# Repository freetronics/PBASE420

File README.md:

Freetronics ProtoBase 420
=========================
Copyright 2015 Freetronics Pty Ltd  
Freetronics site:  www.freetronics.com  
Freetronics email: info@freetronics.com  

ProtoBase 420 is a prototyping circuit board designed to follow the
same format as common 400-point solderless breadboards. It can be
used by soldering parts in place, or a solderless breadboard can be
adhered to the top.

Includes a linear voltage regulator with switchable 3.3V / 5V output,
and a 2.1mm DC jack for power input.

Features:

 * Prototyping area
 * Switchable 3.3V / 5V voltage regulator
 * Power LED
 * 2.1mm DC power socket
 * Overlay guide where you need it (both top and bottom)
 * 3.2mm mounting holes for M3 bolts

You can view more at our product page at:

  http://www.freetronics.com/pbase420

INSTALLATION
------------
The design is saved as an EAGLE project. EAGLE PCB design software is
available from www.cadsoftusa.com free for non-commercial use. To use
this project download it and place the directory containing these files
into the "eagle" directory on your computer. Then open EAGLE and
navigate to Projects -> eagle -> PBASE420.

DISTRIBUTION
------------
The specific terms of distribution of this project are governed by the
license referenced below.

LICENSE
-------
Licensed under the TAPR Open Hardware License (www.tapr.org/OHL).
The "license" folder within this repository also contains a copy of
this license in plain text format.

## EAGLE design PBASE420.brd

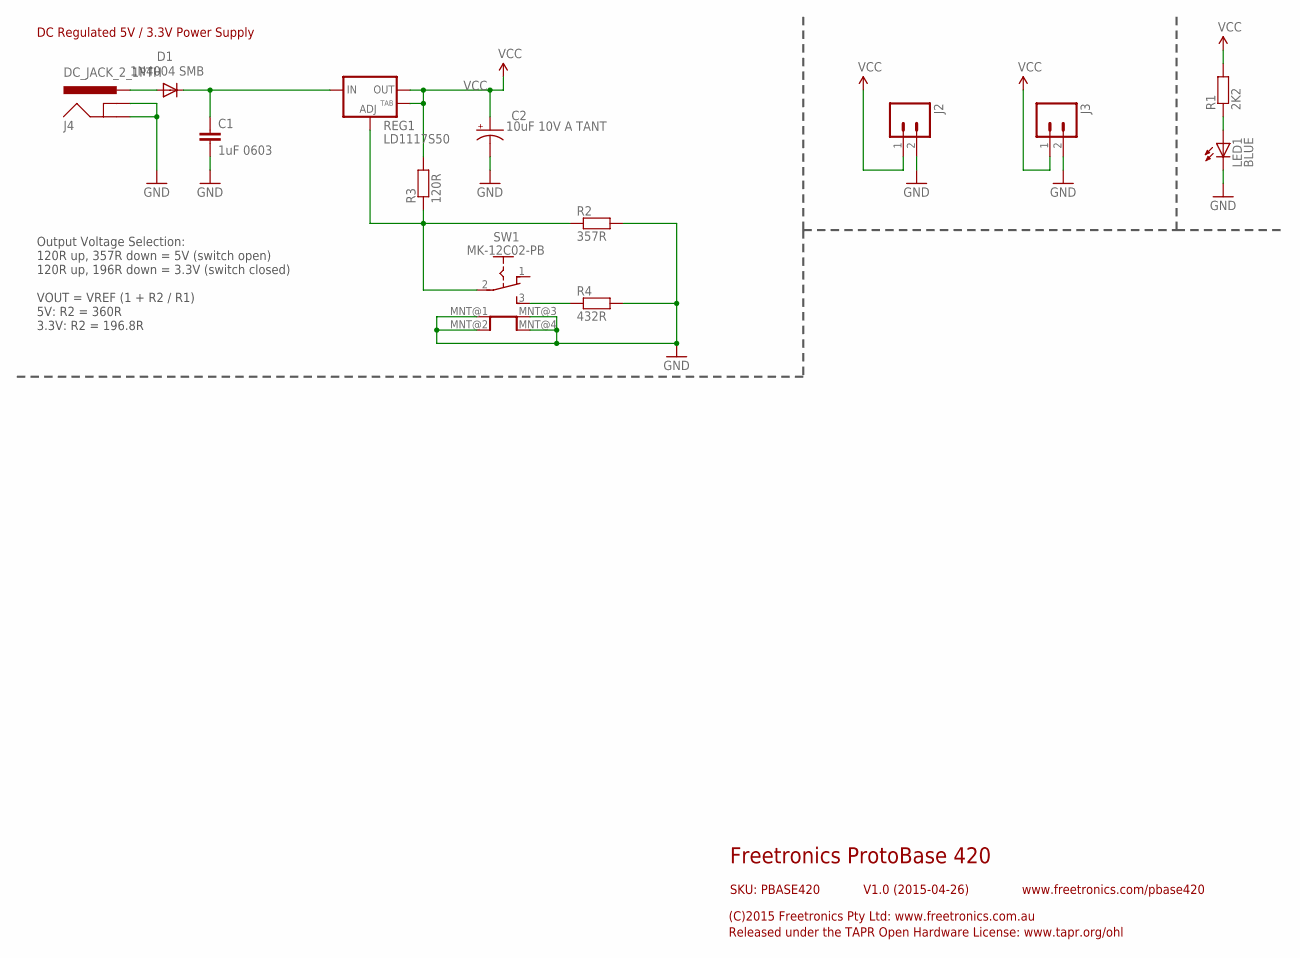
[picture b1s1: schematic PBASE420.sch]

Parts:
C1: 1uF 0603; 0603
C2: 10uF 10V A TANT; EIA3216
D1: 1N4004 SMB; SMB-DIODE
J2, J3: M02PTH; 1X02
J4: DC_JACK_2_1PTH; FREETRONICS_POWER_JACK_PTH
LED1: BLUE; LED-0603
R1: 2K2; 0603
R2: 357R; 0603
R3: 120R; 0603
R4: 432R; 0603
REG1: LD1117S50; SOT223
SW1: MK-12C02-PB; MK-12C02

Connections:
GND: C1.2, C2.C (-), J2.2, J3.2, J4.GND@1 (GND), J4.GND@2 (GND), J4.GNDBREAK@1 (GNDBREAK), J4.GNDBREAK@2 (GNDBREAK), LED1.C, R2.2, R4.2, SW1.MNT@1 (MNT), SW1.MNT@2 (MNT), SW1.MNT@3 (MNT), SW1.MNT@4 (MNT)
unnamed: LED1.A, R1.1
unnamed: R2.1, R3.1, REG1.1 (ADJ), SW1.2 (COM)
unnamed: R4.1, SW1.3 (B)
unnamed: D1.A, J4.PWR@1 (PWR), J4.PWR@2 (PWR)
VCC: C2.A (+), J2.1, J3.1, R1.2, R3.2, REG1.2 (OUT), REG1.4 (OUT)
VIN: C1.1, D1.C, REG1.3 (IN)

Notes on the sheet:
DC Regulated 5V / 3.3V Power Supply
Freetronics ProtoBase 420
V1.0 (2015-04-26)
SKU: PBASE420
(C)2015 Freetronics Pty Ltd: www.freetronics.com.au
Released under the TAPR Open Hardware License: www.tapr.org/ohl
www.freetronics.com/pbase420
Output Voltage Selection: 120R up, 357R down = 5V (switch open) 120R up, 196R down = 3.3V (switch closed) VOUT = VREF (1 + R2 / R1) 5V: R2 = 360R 3.3V: R2 = 196.8R

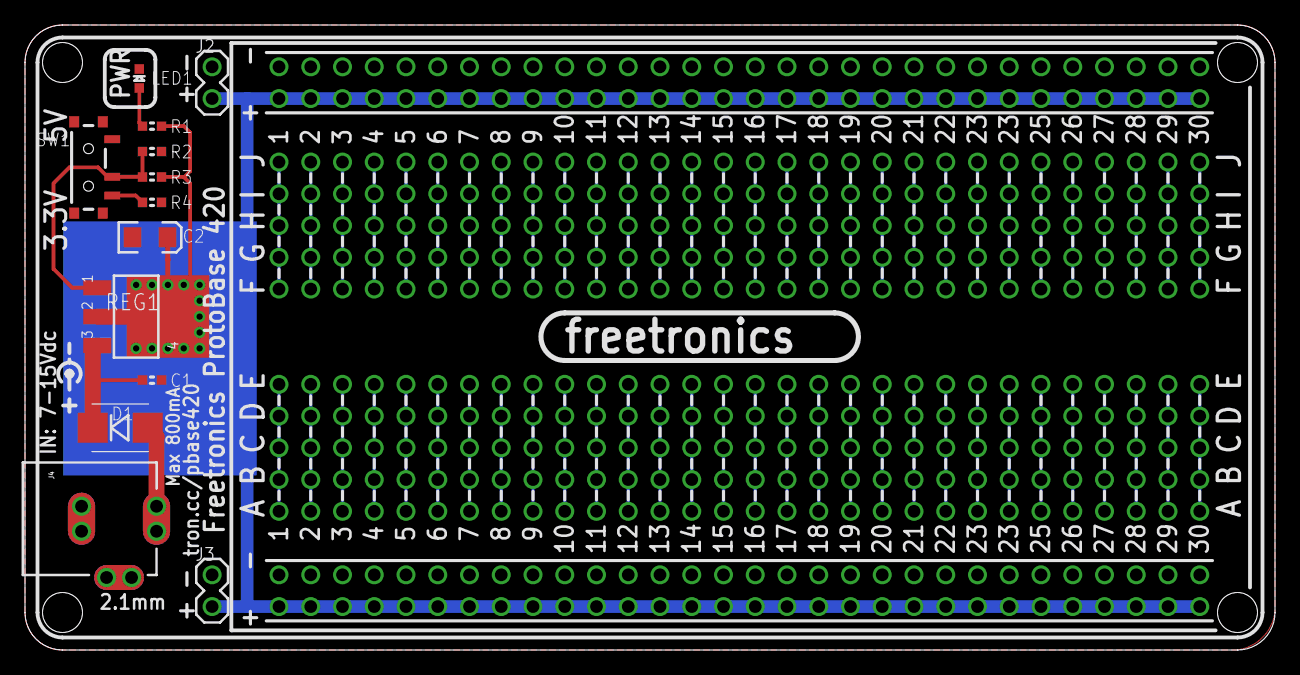
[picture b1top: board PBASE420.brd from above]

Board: 2 copper layers, 100.0 x 50.0 mm, 13 parts (0 on the bottom side), 7 nets.

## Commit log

2015-04-26 Initial project import for v1.0 release
2018-03-28 Updated silkscreen, designators, and README
2018-03-28 Replaced DC jack footprint with slotted version

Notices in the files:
parts and their libraries:
freetronics-original: Licensing: CC v3.0 Share-Alike You are welcome to use this library for commercial purposes.
